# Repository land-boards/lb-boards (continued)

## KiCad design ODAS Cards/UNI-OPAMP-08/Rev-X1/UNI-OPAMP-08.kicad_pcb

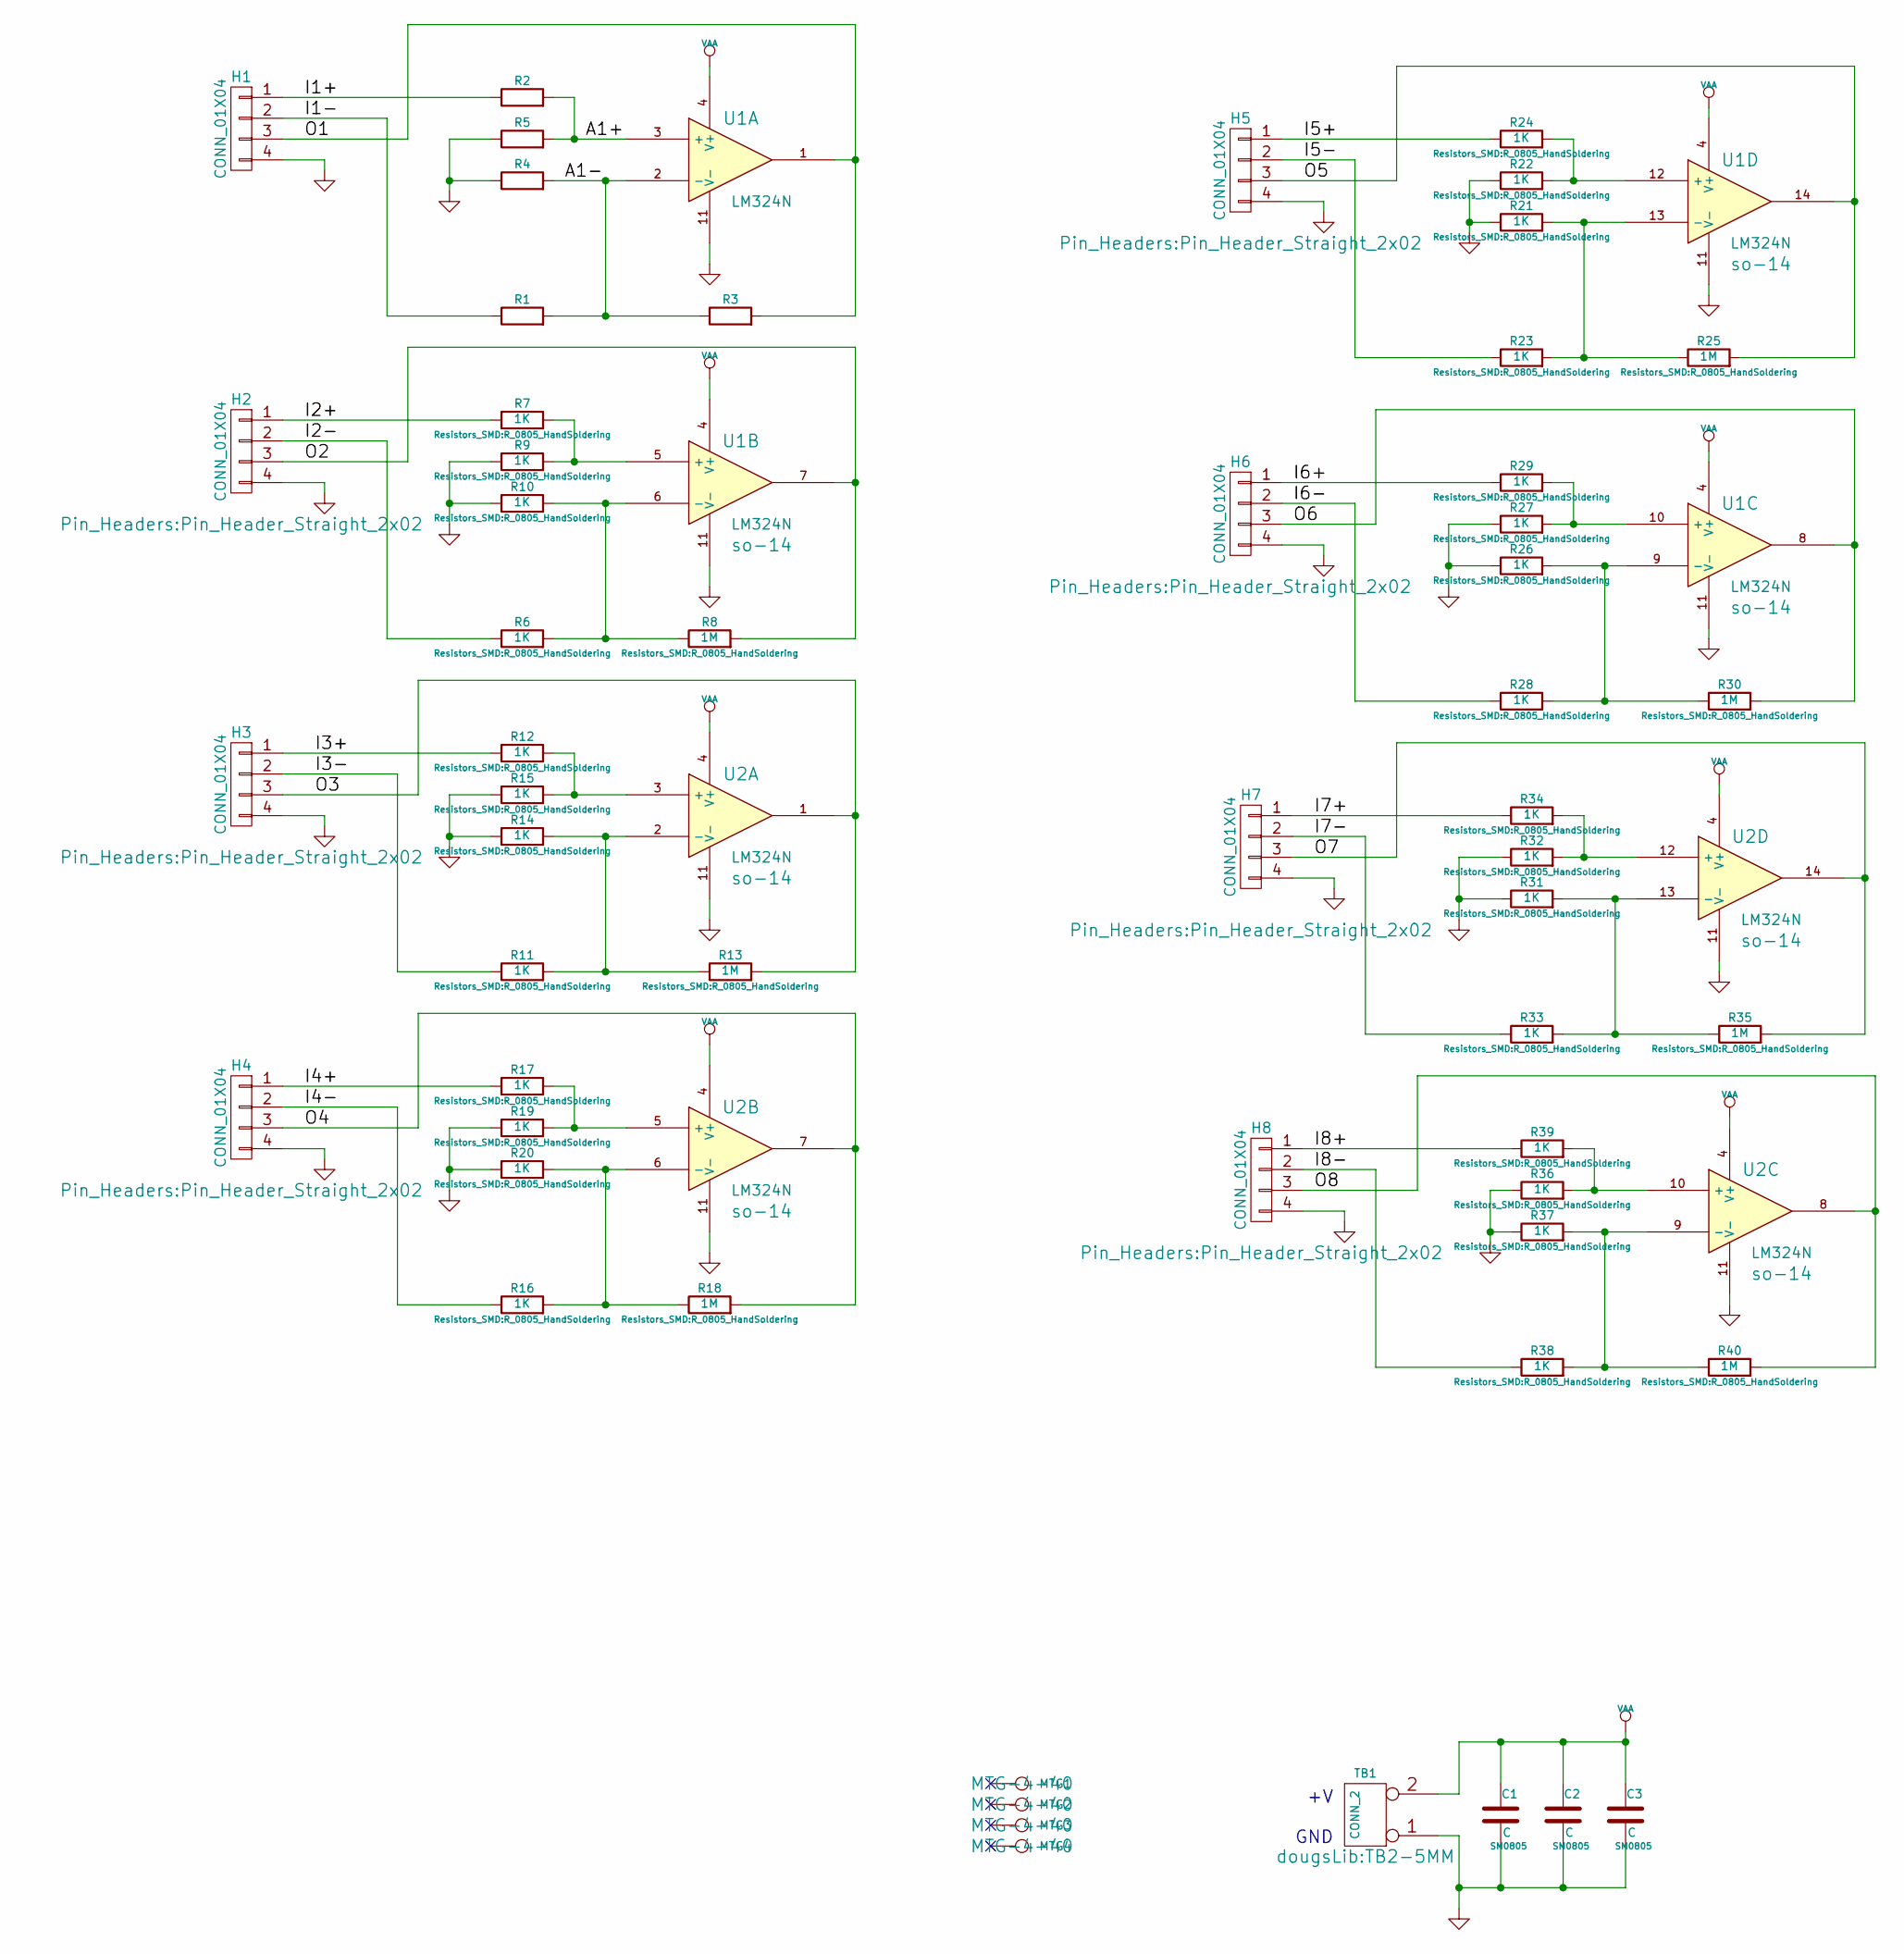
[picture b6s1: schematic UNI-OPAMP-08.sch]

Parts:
C1, C2, C3: C; SM0805
H1, H2, H3, H4, H5, H6, H7, H8: CONN_01X04; Pin_Header_Straight_2x02
MTG1, MTG2, MTG3, MTG4: CONN_1; MTG-4-40
R1, R2, R4, R5, R6, R7, R9, R10, R11, R12, R14, R15, R16, R17, R19, R20, R21, R22, R23, R24, R26, R27, R28, R29, R31, R32, R33, R34, R36, R37, R38, R39: 1K; R_0805_HandSoldering
R3, R8, R13, R18, R25, R30, R35, R40: 1M; R_0805_HandSoldering
TB1: CONN_2; TB2-5MM
U1, U2: LM324N; so-14

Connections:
/I1+: H1.1, R2.1
/I1-: H1.2, R1.1
/I2+: H2.1, R7.1
/I2-: H2.2, R6.1
/I3+: H3.1, R12.1
/I3-: H3.2, R11.1
/I4+: H4.1, R17.1
/I4-: H4.2, R16.1
/I5+: H5.1, R24.1
/I5-: H5.2, R23.1
/I6+: H6.1, R29.1
/I6-: H6.2, R28.1
/I7+: H7.1, R34.1
/I7-: H7.2, R33.1
/I8+: H8.1, R39.1
/I8-: H8.2, R38.1
/O1: H1.3, R3.2, U1.1
/O2: H2.3, R8.2, U1.7
/O3: H3.3, R13.2, U2.1
/O4: H4.3, R18.2, U2.7
/O5: H5.3, R25.2, U1.14
/O6: H6.3, R30.2, U1.8
/O7: H7.3, R35.2, U2.14
/O8: H8.3, R40.2, U2.8
GND: C1.2, C2.2, C3.2, H1.4, H2.4, H3.4, H4.4, H5.4, H6.4, H7.4, H8.4, R4.1, R5.1, R9.1, R10.1, R14.1, R15.1, R19.1, R20.1, R21.1, R22.1, R26.1, R27.1, R31.1, R32.1, R36.1, R37.1, TB1.1, U1.11 (V-), U2.11 (V-)
unnamed: R1.2, R3.1, R4.2, U1.2 (-)
unnamed: R2.2, R5.2, U1.3 (+)
unnamed: R7.2, R9.2, U1.5 (+)
unnamed: R6.2, R8.1, R10.2, U1.6 (-)
unnamed: R11.2, R13.1, R14.2, U2.2 (-)
unnamed: R12.2, R15.2, U2.3 (+)
unnamed: R16.2, R18.1, R20.2, U2.6 (-)
unnamed: R17.2, R19.2, U2.5 (+)
unnamed: R21.2, R23.2, R25.1, U1.13 (-)
unnamed: R22.2, R24.2, U1.12 (+)
unnamed: R26.2, R28.2, R30.1, U1.9 (-)
unnamed: R27.2, R29.2, U1.10 (+)
unnamed: R31.2, R33.2, R35.1, U2.13 (-)
unnamed: R32.2, R34.2, U2.12 (+)
unnamed: R36.2, R39.2, U2.10 (+)
unnamed: R37.2, R38.2, R40.1, U2.9 (-)
VAA: C1.1, C2.1, C3.1, TB1.2 (PM), U1.4 (V+), U2.4 (V+)

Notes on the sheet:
+V GND

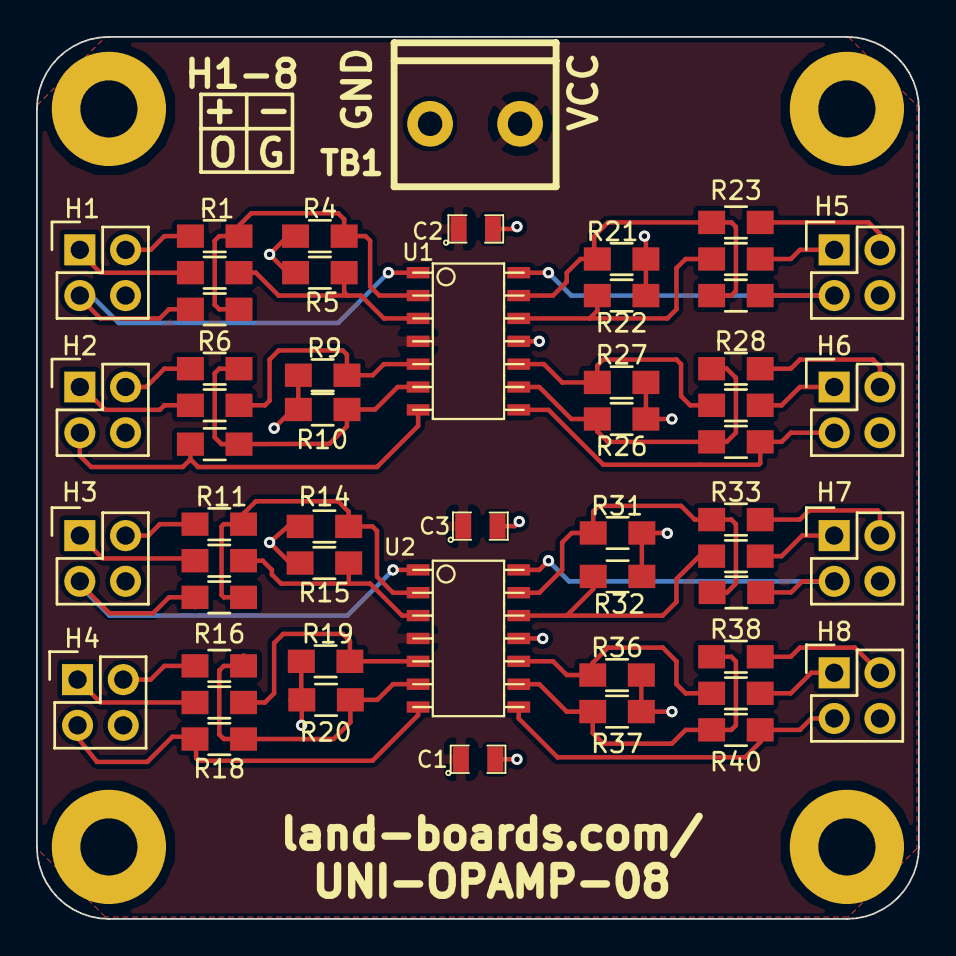
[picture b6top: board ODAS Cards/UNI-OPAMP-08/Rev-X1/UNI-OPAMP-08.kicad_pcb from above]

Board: 2 copper layers, 49.0 x 49.0 mm, 58 parts (0 on the bottom side), 42 nets.

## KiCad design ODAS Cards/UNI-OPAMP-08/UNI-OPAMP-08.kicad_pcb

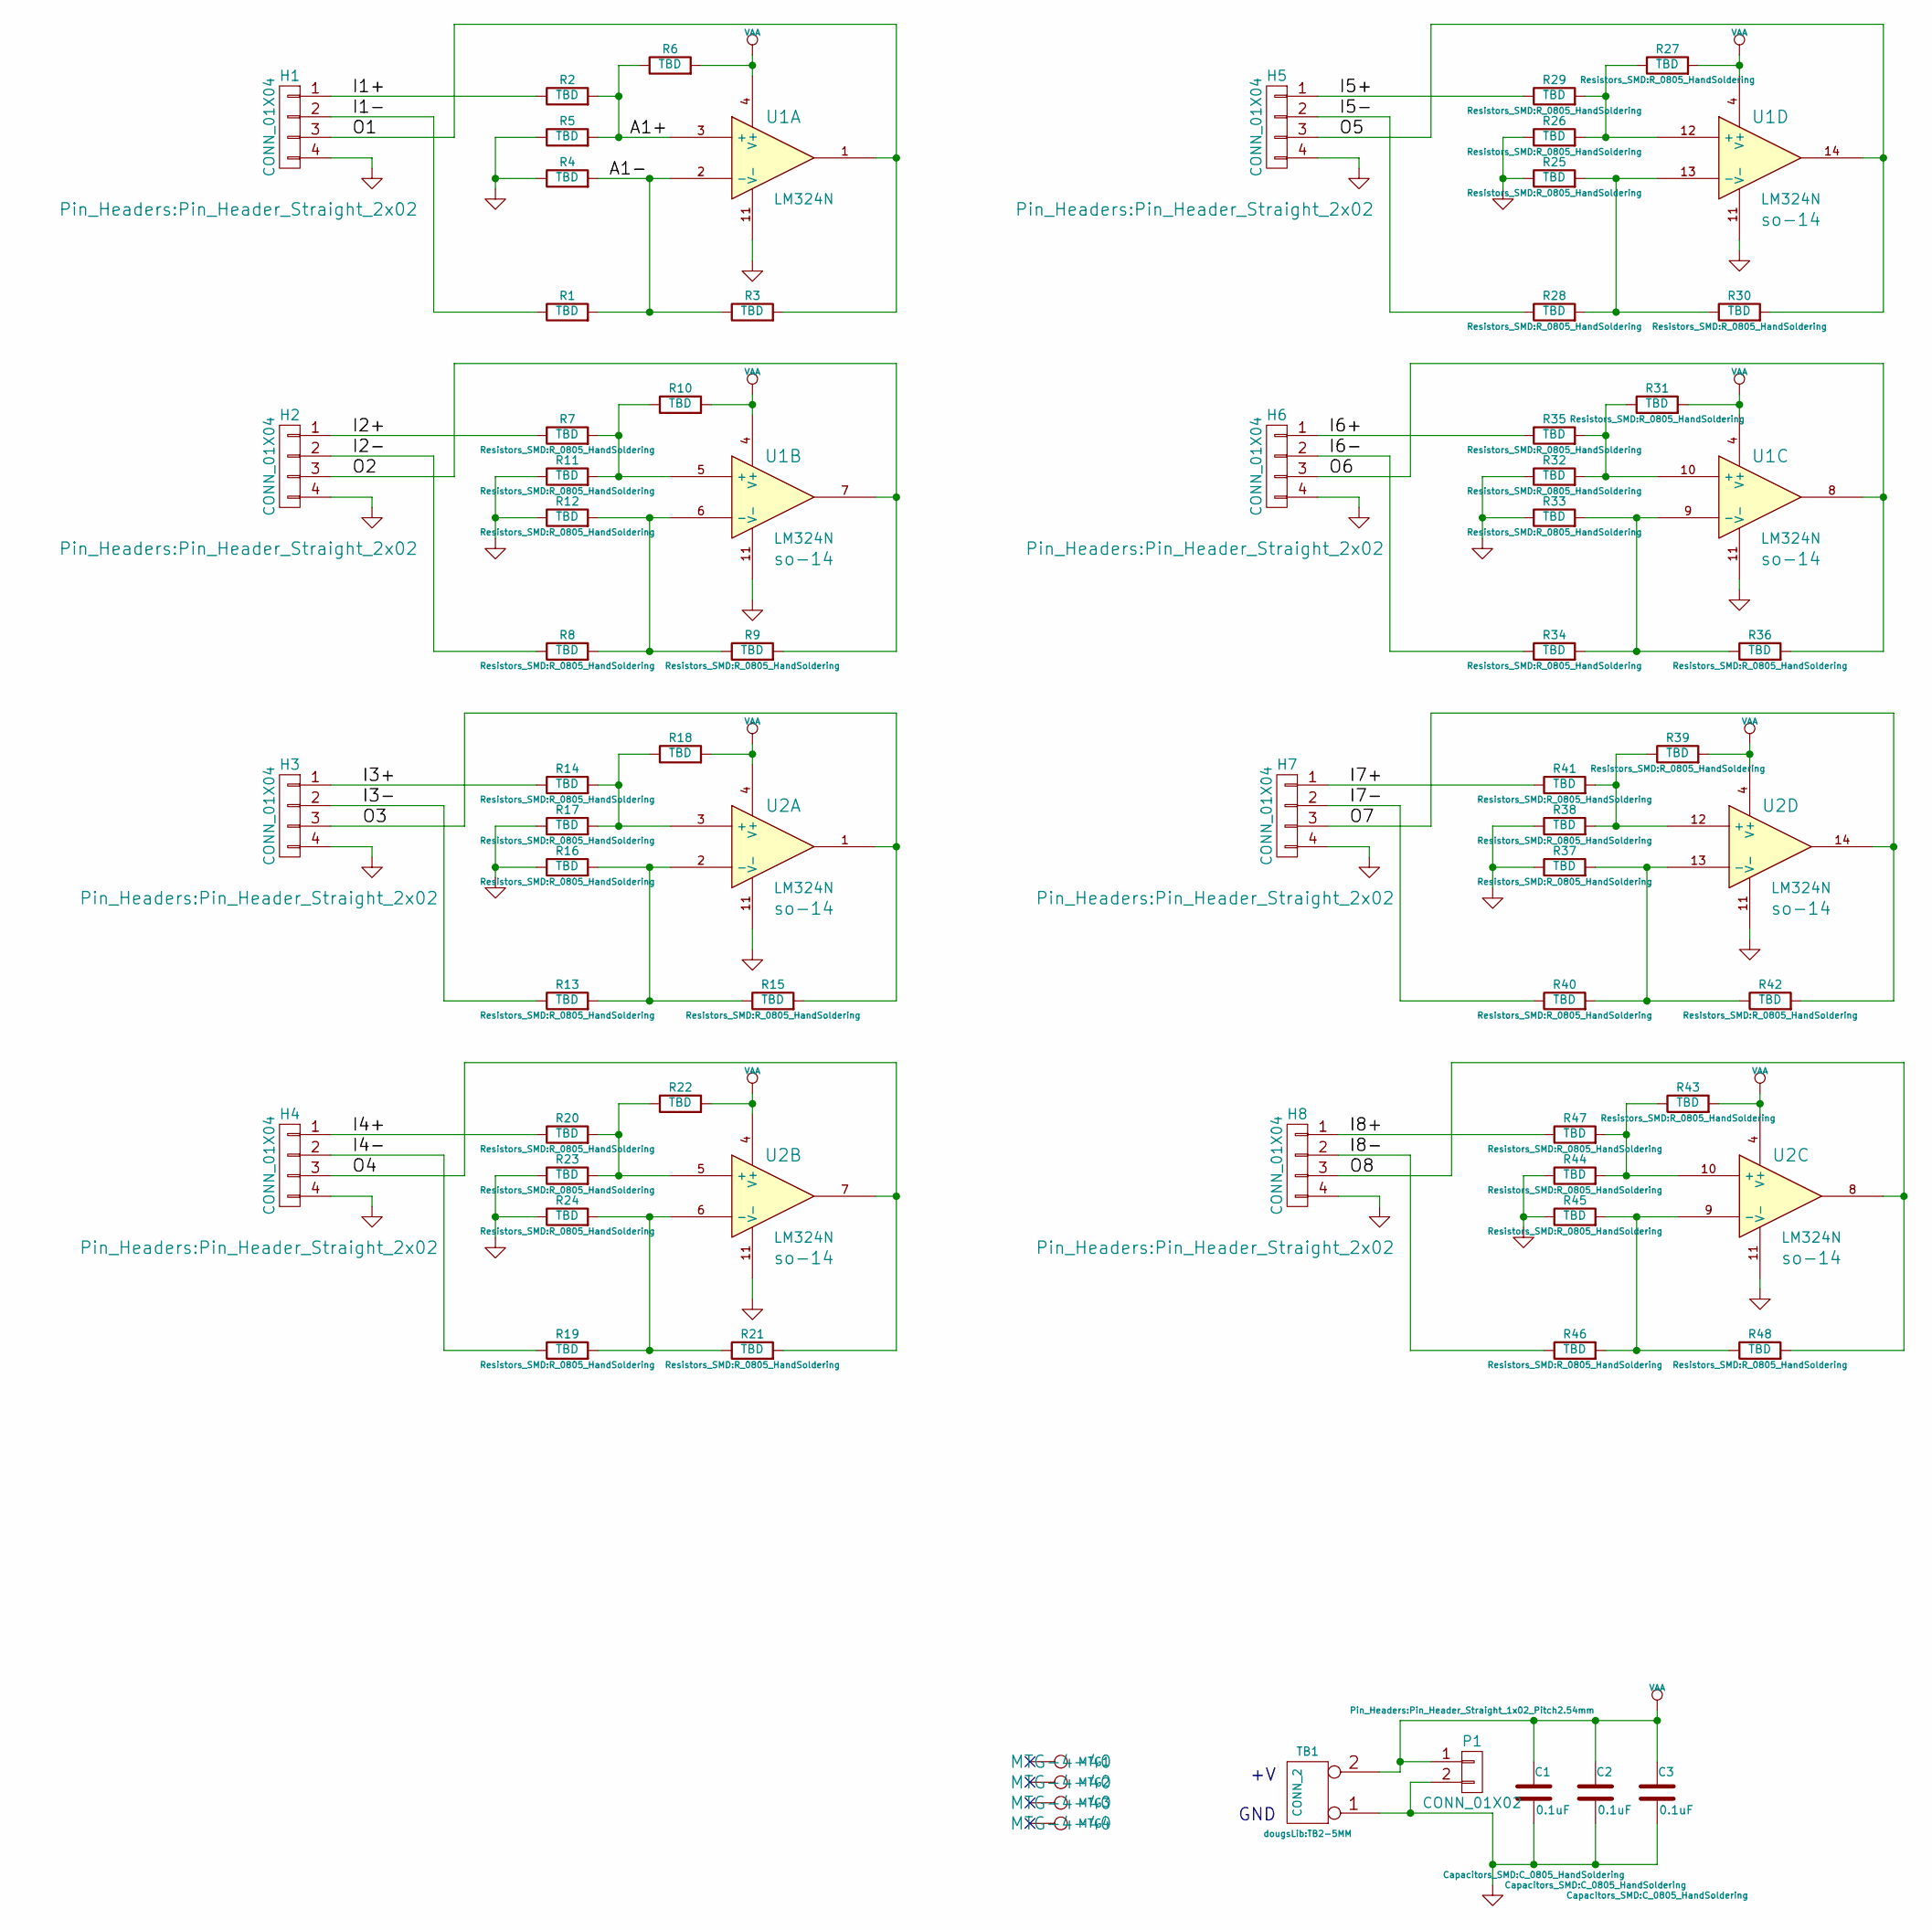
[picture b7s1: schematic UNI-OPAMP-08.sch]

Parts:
C1, C2, C3: 0.1uF; C_0805_HandSoldering
H1, H2, H3, H4, H5, H6, H7, H8: CONN_01X04; Pin_Header_Straight_2x02
MTG1, MTG2, MTG3, MTG4: CONN_1; MTG-4-40
P1: CONN_01X02; Pin_Header_Straight_1x02_Pitch2.54mm
R1, R2, R3, R4, R5, R6, R7, R8, R9, R10, R11, R12, R13, R14, R15, R16, R17, R18, R19, R20, R21, R22, R23, R24, R25, R26, R27, R28, R29, R30, R31, R32, R33, R34, R35, R36, R37, R38, R39, R40, R41, R42, R43, R44, R45, R46, R47, R48: TBD; R_0805_HandSoldering
TB1: CONN_2; TB2-5MM
U1, U2: LM324N; so-14

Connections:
/A1+: R2.2, R5.2, R6.1, U1.3 (+)
/A1-: R1.2, R3.1, R4.2, U1.2 (-)
/I1+: H1.1, R2.1
/I1-: H1.2, R1.1
/I2+: H2.1, R7.1
/I2-: H2.2, R8.1
/I3+: H3.1, R14.1
/I3-: H3.2, R13.1
/I4+: H4.1, R20.1
/I4-: H4.2, R19.1
/I5+: H5.1, R29.1
/I5-: H5.2, R28.1
/I6+: H6.1, R35.1
/I6-: H6.2, R34.1
/I7+: H7.1, R41.1
/I7-: H7.2, R40.1
/I8+: H8.1, R47.1
/I8-: H8.2, R46.1
/O1: H1.3, R3.2, U1.1
/O2: H2.3, R9.2, U1.7
/O3: H3.3, R15.2, U2.1
/O4: H4.3, R21.2, U2.7
/O5: H5.3, R30.2, U1.14
/O6: H6.3, R36.2, U1.8
/O7: H7.3, R42.2, U2.14
/O8: H8.3, R48.2, U2.8
GND: C1.2, C2.2, C3.2, H1.4, H2.4, H3.4, H4.4, H5.4, H6.4, H7.4, H8.4, P1.2, R4.1, R5.1, R11.1, R12.1, R16.1, R17.1, R23.1, R24.1, R25.1, R26.1, R32.1, R33.1, R37.1, R38.1, R44.1, R45.1, TB1.1, U1.11 (V-), U2.11 (V-)
unnamed: R7.2, R10.1, R11.2, U1.5 (+)
unnamed: R8.2, R9.1, R12.2, U1.6 (-)
unnamed: R13.2, R15.1, R16.2, U2.2 (-)
unnamed: R14.2, R17.2, R18.1, U2.3 (+)
unnamed: R19.2, R21.1, R24.2, U2.6 (-)
unnamed: R20.2, R22.1, R23.2, U2.5 (+)
unnamed: R25.2, R28.2, R30.1, U1.13 (-)
unnamed: R26.2, R27.1, R29.2, U1.12 (+)
unnamed: R31.1, R32.2, R35.2, U1.10 (+)
unnamed: R33.2, R34.2, R36.1, U1.9 (-)
unnamed: R37.2, R40.2, R42.1, U2.13 (-)
unnamed: R38.2, R39.1, R41.2, U2.12 (+)
unnamed: R43.1, R44.2, R47.2, U2.10 (+)
unnamed: R45.2, R46.2, R48.1, U2.9 (-)
VAA: C1.1, C2.1, C3.1, P1.1, R6.2, R10.2, R18.2, R22.2, R27.2, R31.2, R39.2, R43.2, TB1.2 (PM), U1.4 (V+), U2.4 (V+)

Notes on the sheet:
+V GND

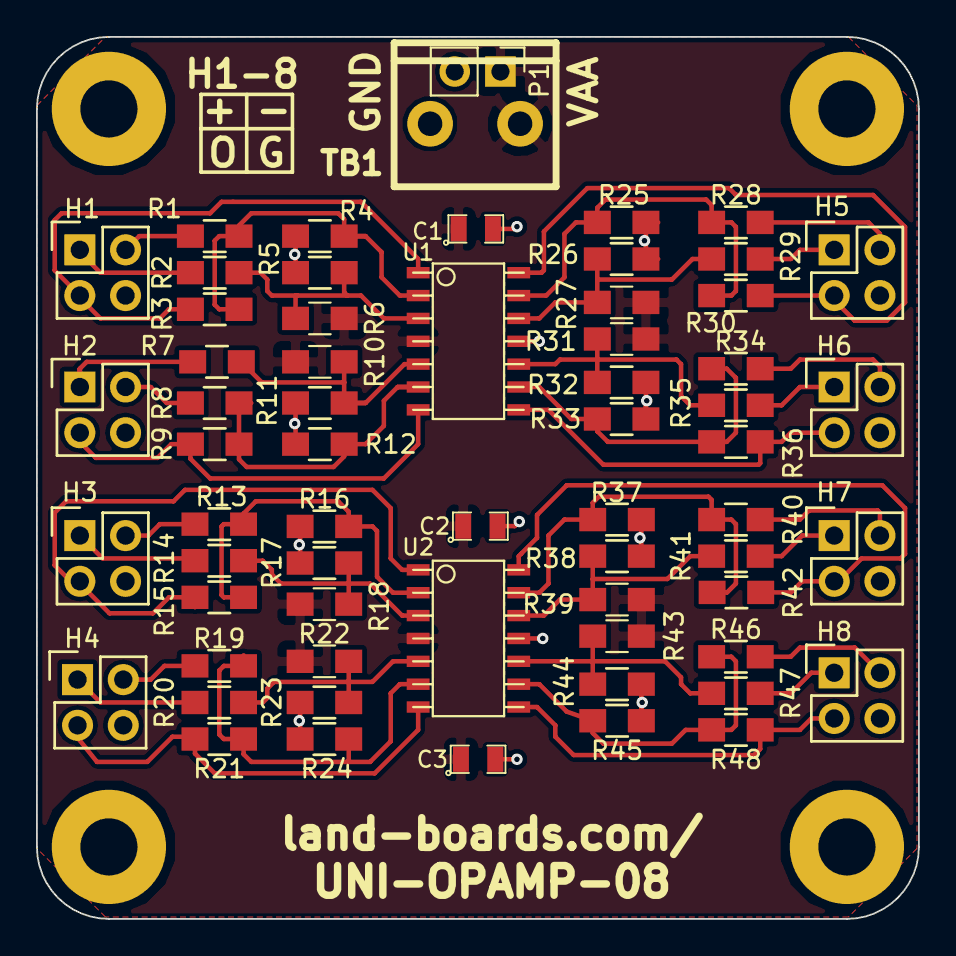
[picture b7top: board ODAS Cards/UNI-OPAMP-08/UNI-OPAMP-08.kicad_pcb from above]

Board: 2 copper layers, 49.0 x 49.0 mm, 67 parts (0 on the bottom side), 42 nets.
